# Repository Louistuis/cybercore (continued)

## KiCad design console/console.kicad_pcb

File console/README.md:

# CyberCore Console (rev 0.2, proof of concept)

A slim, black, console-sized box that runs **DeepSeek V3.1 (671B)** locally, on our own carrier board with
**4 × NVIDIA Jetson T5000 (AGX Thor) modules**. Each module has 128 GB of memory, so there is **512 GB in total**.

## What's on the board
| Block | What | Status |
|---|---|---|
| Compute | 4 × Jetson T5000 module (87 × 100 mm), 699-pin Molex Mirror Mezz 203456-0003, 2.5 mm connector = **5 mm** between board and module | Pin map **real** (NVIDIA). Contact grid **real** (Molex drawing 2034560003). Outline, connector position and standoffs **measured** from NVIDIA's drawings |
| Memory | 4 × 128 GB LPDDR5X = 512 GB (273 GB/s per module, per NVIDIA's spec) | On the modules |
| Module-to-module | Full mesh: each module's MGBE C0-C2 (UPHY lanes 12-14) wired straight to the 3 others, 6 links, AC caps on the back | Nets real, routed by the autorouter (not yet length-matched) |
| Network clock | One 156.25 MHz HCSL oscillator per module (SCTF SX5DF156.250B20F30HNN) into UPHY_REFCLK2, terminated as in DG-12084 fig. 7-12 (33.2 Ω series, 49.9 Ω to GND) | **Real**: pinout and land pattern from SCTF's 5Z spec sheet, which asks for the same 33 Ω / 50 Ω load |
| Uplink | Each module's MGBE C3 → one lane of a QSFP28 cage (4 × 25G breakout = one port per module). TE 2170704 press-fit cage + 38-pin connector, cage end at the rear edge | **Real**: cage layout from TE's drawing 2170704 rev G8, contact pads from SFF-8662 table 6-3 |
| Storage | 1 × M.2 2280 NVMe per module on the back (PCIe C5 x4, UPHY lanes 8-11), each holding its share of the model | Nets real, stock footprint |
| Power | 12 V in through 2 × EPS-style Mini-Fit Jr 8-pin (~600 W). See the power section | Real TI parts and land patterns |
| Management | Per module: 2×20 1.27 mm header (sequencing, reset, recovery, thermal, debug UART, I2C, eFuse enables). One system header: buck enable, PMBus, power-good, current monitors, QSFP sideband | Real connectors. The management board that plugs in is in `../mgmt/` |
| Service | 4 × USB-C on the rear (each module's USB0, used for recovery and flashing) | Real |
| Front | The black **CyberCore status panel** (`../panel/`) plugs into J3 (module 0's USB1 + 5 V) | Panel is finished and orderable |
| Cooling | 4 fan headers, each module driving its own blower (FAN_PWM / FAN_TACH) | Real connectors; the thermal design is not done |

Board: 240 × 256 mm, 12 layers (HDI rules: 0.10 mm clearance), 1.6 mm, **black solder mask, ENIG**.
With the 2.5 mm connector, NVIDIA allows **no parts under a module** on the top side. The module footprint carries a keep-out rule area, so DRC fails if anything lands there.
Everything that belongs to a module (eFuses, load switch, clock, AC caps, M.2 drive, management header) sits on the **back**, right under it.

## Power
| Rail | Part | Setting |
|---|---|---|
| 12 V → 5 V, 20 A | TI **TPS546B24A** (LQFN-CLIP-40, LCSC C3189423) + Coilcraft XAL7070 1 µH, 6 × 47 µF out | Pin straps: 5.0 V, 550 kHz, 3 ms soft start, compensation config 23 (TI's procedure), PMBus 0x10. Enabled by management |
| 12 V → 3.3 V, 20 A | TI **TPS546B24A**, same power stage | Pin straps: 3.32 V, PMBus 0x11. Always on (standby rail), starts at ~8.4 V in |
| Module SYS_VIN_HV (12 V) | TI **TPS25982** eFuse per module (VQFN-24, LCSC C2155761) | 13.4 A limit (T5000 ≈ 130 W ≈ 11 A), latch-off on fault, current monitor to the system header |
| Module SYS_VIN_MV (5 V) | TI **TPS25982** per module | 6.5 A limit, just above NVIDIA's 6 A absolute maximum (DS-11945 table 6-2) |
| Module SYS_VIN_SV (3.3 V) | TI **TPS22918** load switch per module (SOT-23-6, LCSC C131941) | Quick output discharge on, so SV falls after HV and MV |

Each converter's footprint was drawn from TI's own land-pattern drawing (RVF0040A, RGE0024M). The strap resistor values come from the TPS546B24A datasheet tables.

## The model math (DeepSeek V3.1)
- **Size:** 671B parameters at 4-bit ≈ 380-400 GB.
  - 512 GB minus each module's OS share leaves ~460 GB, so it fits with ~50 GB for context cache.
  - 8-bit (~700 GB) does **not** fit.
- **Per token:** 37B active parameters ≈ 18.5 GB read per token.
- **Speed:**
  - Layers split across the 4 modules (pipeline): one module works at a time, so the ceiling is 273 GB/s ÷ 18.5 GB ≈ **15 tok/s**.
  - Experts split across all 4 modules working at once over the 25G mesh: the ceiling is ~1.1 TB/s ÷ 18.5 GB ≈ **59 tok/s**. Mesh latency on every layer eats into that.
  - **Estimate: about 10-25 tok/s for one user.** Measure it before believing it.
  - For scale: a 512 GB Apple Mac Studio does ~17-25 tok/s on this model, and hosted datacenter services ~200.
- **Power:** ~520 W for the modules at full power + NVMe + fans ≈ 600 W.
- **Module cost:** NVIDIA lists the T5000 at $4,999 each (1,000-unit price), so ~$20k for 4 before the board and case.

## Build status (honest)
**Real now:**
- Board outline and the 12-layer black stackup
- Every connection the board makes to each module's 699 pins, taken from NVIDIA's pin description spreadsheet: power, GND, PCIe, MGBE, MGBE clock, USB, management
- Module outline, connector position and the 4 standoff holes, measured from NVIDIA's drawings
- Power: TI bucks, eFuses and load switches with their real land patterns and set-up resistors
- MGBE clock: SCTF oscillator with the maker's pinout and land pattern (pin 1 = enable, high or open runs it)
- QSFP28: TE 2170704 cage layout (sheet 15) with SFF-8662 contact pads: 2 alignment holes, 12 press-fit cage holes, 38 contacts and the cage keep-out, which DRC enforces
- Mirror Mezz contact grid from Molex's drawing
- Stock connectors (M.2, USB-C, Mini-Fit Jr, fan headers, management headers)
- DRC of the placed board (`console.kicad_pcb`): 0 violations
- **Routed** (`console_routed.kicad_pcb`): every connection made, 0 unconnected. See the routing section below

**Confirmed from the makers' own documents:**
- Mirror Mezz contact grid: Molex drawing 2034560003 sheet 2. 699 round 0.50 mm pads (0.60 mm mask opening), rows 1.50 mm apart, 0.90 mm pitch with a 1.30 mm gap between pair groups, alternate rows shifted 0.20 mm. This replaced the uniform 0.96 mm grid measured from NVIDIA's pictures, which was off by up to 0.4 mm.
- QSFP28 contact pads: 0.35 × 1.80 mm, SFF-8662 rev 2.9 table 6-3, which also matches every position measured from TE's drawing.
- 5 V module current: NVIDIA DS-11945 v1.4 table 6-2 gives 6 A absolute maximum, so the eFuse limit is now 6.5 A (226 Ω).

**Still to check:**
1. **Buck compensation (bench).** Config 23 (current-loop gain 6, voltage-loop gain 2) follows TI's procedure in the TPS546B24A datasheet (section 8.2.2.10). It is a stable starting point; measure gain and phase margin on the first board, then raise the gains over PMBus.
2. **MV_LSW_MON (pin L42).** NVIDIA's pin spreadsheet names it but no document describes it, so it is left unconnected. Ask NVIDIA before ordering.
3. **Module position (±0.5 mm).** The connector's place on the module and the standoff holes are still measured from NVIDIA's drawings. NVIDIA's reference carrier design files would pin these down exactly.

**Open questions:**
- **The direct MGBE-to-MGBE mesh.** XFI is meant to drive an SFP+ module. A short PCB link acts like a passive copper cable, but it must be checked against design guide section 7.3.
- **25 GbE speed.** NVIDIA says it is "being validated", so plan on 10G per link until it is confirmed.
- **Sequencing.** Every module has its own SYS_VIN_SV → MV/HV → MODULE_POWER_ON sequence (DG-12084 chapter 5). The eFuses and switches are on this board; the logic that drives them is on the management board (`../mgmt/SEQUENCING.md`).
- **Cooling.** ~540 W in a slim box. The enclosure concept and its hand-calculated cooling budget are in `../enclosure/`; there is no thermal simulation yet.

**Not done:** signal-integrity routing of the high-speed pairs (see below), and power and thermal simulation.

## Routing

The signal layers (F.Cu, In2, In4, In10, B.Cu) of `console_routed.kicad_pcb`. The other 7 layers are ground and power planes, with one 5 V and one 20 V island per module.

- **All 502 connections routed** by Freerouting in 5 passes (7 h 50 min on one CPU core). KiCad's DRC finds **0 unconnected items, 0 clearance errors**.
- **70 track segments are thinner than the 0.09 mm board minimum** (53 mm in all, most under 0.5 mm long). They're where the autorouter narrowed a track to leave a fine-pitch pad, mostly at the Mirror Mezz connectors. 65 are 0.075 mm, which HDI fabs make, and 5 are 0.05-0.06 mm, which need a hand fix. `route_finish.py` already widened every segment that had room.
- **Not signal-integrity routed.** The autorouter routes each wire of a differential pair on its own. The 25G mesh, PCIe Gen4, USB and QSFP pairs still need routing as coupled, impedance-controlled and length-matched pairs. Treat this file as proof that the board can be fully connected on 12 layers, not as an orderable layout.

## Rebuild
1. Download NVIDIA's *Jetson Thor Series Modules Design Guide* (DG-12084-001, free from developer.nvidia.com).
2. Extract its attachments: `pdfdetach -saveall -o datasheets/nv_attach <guide.pdf>`.
3. Run the build script with KiCad's Python:
```
/Applications/KiCad/KiCad.app/Contents/Frameworks/Python.framework/Versions/Current/bin/python3 make_console.py
kicad-cli pcb drc -o drc.rpt console.kicad_pcb
```
4. Route it (about 8 hours on one core; commands in `route.py`): `route.py prep`, then Freerouting, then `route.py import` and `route_finish.py`.
NVIDIA's documents and the pin spreadsheet are **not** in this repo; the script reads them from your own download. The TI datasheets used for the power stage are free on ti.com (TPS546B24A, TPS25982, TPS22918). The QSFP28 layout comes from TE's customer drawing 2170704 (te.com) and SFF-8662 (snia.org); the connector grid from Molex drawing 2034560003 (molex.com).

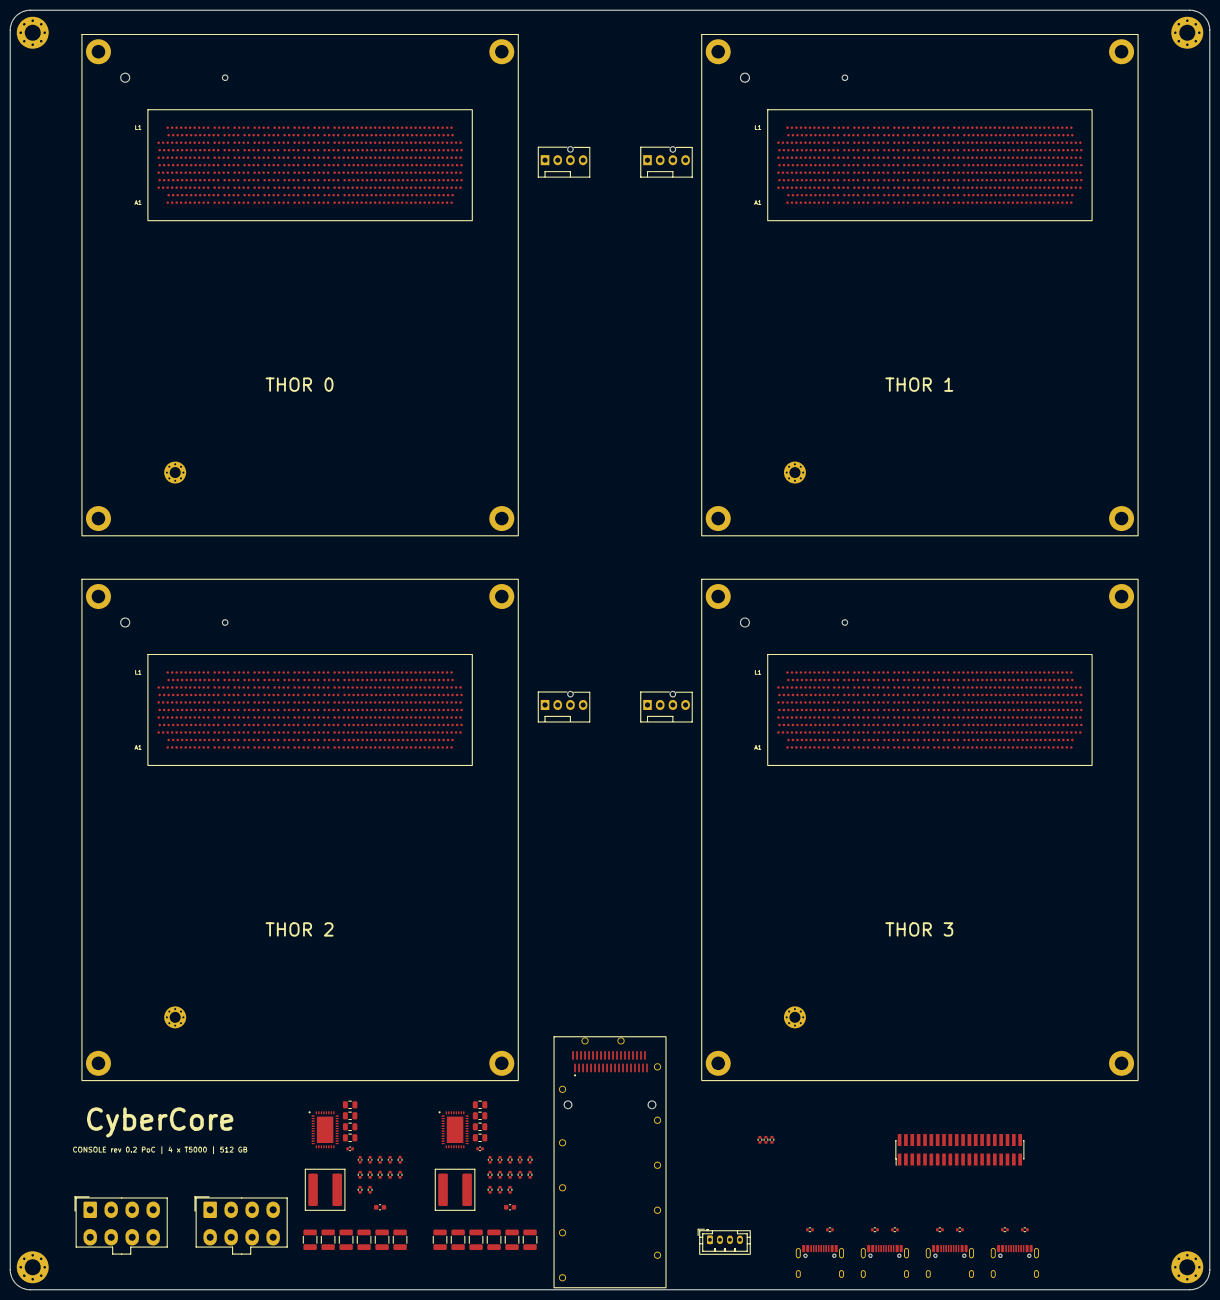
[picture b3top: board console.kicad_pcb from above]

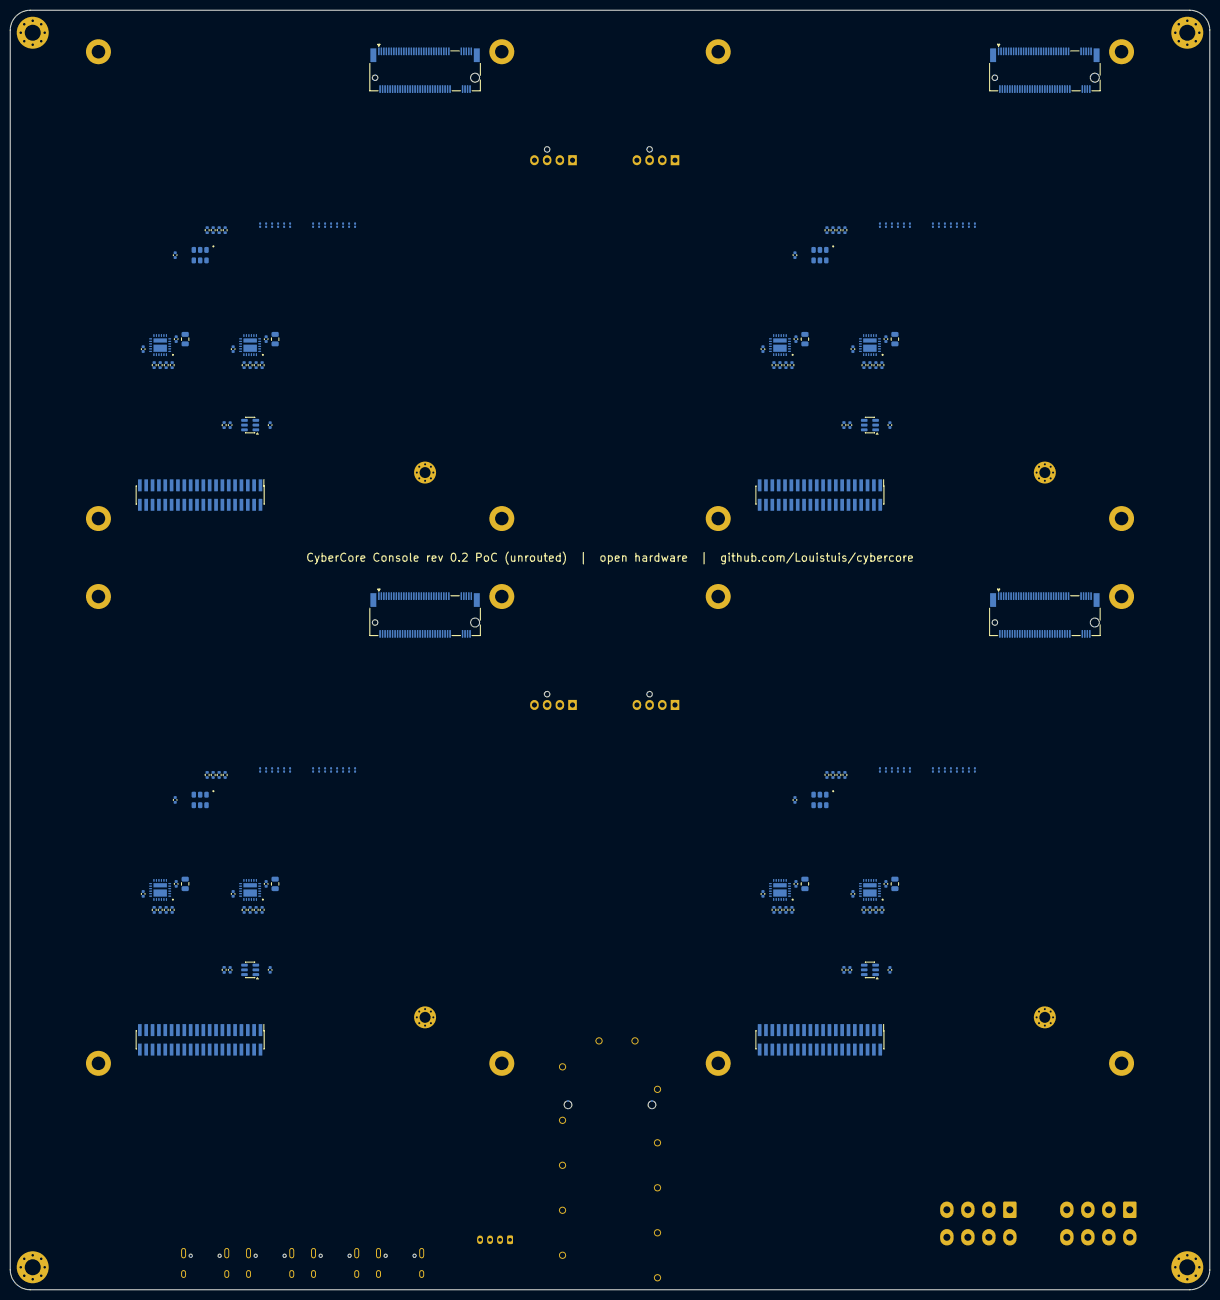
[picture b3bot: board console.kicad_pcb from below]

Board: 12 copper layers, 240.0 x 256.0 mm, 257 parts (172 on the bottom side), 384 nets, no tracks yet.

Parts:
C101, C111, C201, C211, C301, C311, C401, C411, C501, C502, C503, C504, C601, C602, C603, C604: 22uF; C_0805_2012Metric
C102, C112, C140, C202, C212, C240, C302, C312, C340, C402, C412, C440, C522, C622: 100nF; C_0402_1005Metric
C103, C203, C303, C403, C505, C605: 10nF; C_0402_1005Metric
C113, C213, C313, C413: 3.3nF; C_0402_1005Metric
C121, C221, C321, C421, C521, C523, C621, C623: 1uF; C_0402_1005Metric
C122, C222, C322, C422: 1nF; C_0402_1005Metric
C150, C151, C152, C153, C154, C155, C156, C157, C158, C159, C160, C161, C162, C163, C250, C251, C252, C253, C254, C255, C256, C257, C258, C259, C260, C261, C262, C263, C350, C351, C352, C353, C354, C355, C356, C357, C358, C359, C360, C361, C362, C363, C450, C451, C452, C453, C454, C455, C456, C457, C458, C459, C460, C461, C462, C463: 100nF; C_0201_0603Metric
C511, C512, C513, C514, C515, C516, C611, C612, C613, C614, C615, C616: 47uF; C_1210_3225Metric
C531, C631: 4.7uF; C_0603_1608Metric
H1, H2, H3, H4: case; MountingHole_3.2mm_M3_Pad_Via
H10, H11, H12, H13: M.2 standoff; MountingHole_2.2mm_M2_Pad_Via
J1, J5: 12V IN (EPS 8-pin); Molex_Mini-Fit_Jr_5566-08A_2x04_P4.20mm_Vertical
J2: QSFP28 4x25G uplink; TE_2170704_QSFP28_Cage_SFF8679_38P
J3: STATUS PANEL; JST_PH_B4B-PH-K_1x04_P2.00mm_Vertical
J4: SYS MGMT; PinHeader_2x20_P1.27mm_Vertical_SMD
J10, J11, J12, J13: M.2 2280 NVMe 4 TB; TE_M.2_M_2x38-1MP_P0.5mm
J20: MGMT M0; PinHeader_2x20_P1.27mm_Vertical_SMD
J21: MGMT M1; PinHeader_2x20_P1.27mm_Vertical_SMD
J22: MGMT M2; PinHeader_2x20_P1.27mm_Vertical_SMD
J23: MGMT M3; PinHeader_2x20_P1.27mm_Vertical_SMD
J30: FAN M0; FanPinHeader_1x04_P2.54mm_Vertical
J31: FAN M1; FanPinHeader_1x04_P2.54mm_Vertical
J32: FAN M2; FanPinHeader_1x04_P2.54mm_Vertical
J33: FAN M3; FanPinHeader_1x04_P2.54mm_Vertical
J40: USB-C M0 recovery; USB_C_Receptacle_HRO_TYPE-C-31-M-12
J41: USB-C M1 recovery; USB_C_Receptacle_HRO_TYPE-C-31-M-12
J42: USB-C M2 recovery; USB_C_Receptacle_HRO_TYPE-C-31-M-12
J43: USB-C M3 recovery; USB_C_Receptacle_HRO_TYPE-C-31-M-12
L501, L601: XAL7070-102MEC 1uH (C6609502); L_Coilcraft_XAL7070-XXX
R10, R11, R12, R13, R14, R15, R16, R17: 5.1k; R_0402_1005Metric
R101, R201, R301, R401: 110; R_0402_1005Metric
R102, R202, R302, R402: 470; R_0402_1005Metric
R103, R113, R121, R203, R213, R221, R303, R313, R321, R403, R413, R421, R503, R603: 100k; R_0402_1005Metric
R104, R114, R204, R214, R304, R314, R404, R414, R502, R602, R703: 10k; R_0402_1005Metric
R111, R211, R311, R411: 226; R_0402_1005Metric
R112, R212, R312, R412: 1k; R_0402_1005Metric
R140, R141, R240, R241, R340, R341, R440, R441: 33.2; R_0402_1005Metric
R142, R143, R242, R243, R342, R343, R442, R443: 49.9; R_0402_1005Metric
R501, R601: 10; R_0402_1005Metric
R504: 1.87k; R_0402_1005Metric
R505, R605: 12.1k; R_0402_1005Metric
R506, R607: 56.2k; R_0402_1005Metric
R507, R608: 11.5k; R_0402_1005Metric
R508, R509, R609: 4.64k; R_0402_1005Metric
R604: 15k; R_0402_1005Metric
R606: 21.5k; R_0402_1005Metric
R610: 5.62k; R_0402_1005Metric
R701, R702: 4.7k; R_0402_1005Metric
U1, U2, U3, U4: Jetson T5000 (AGX Thor) 128 GB; Jetson_T5000_Module_MirrorMezz699_Carrier
U101, U102, U201, U202, U301, U302, U401, U402: TPS259827ONRGER (C2155761); TI_RGE0024M_VQFN-24_4x4mm_P0.5mm_SplitPad
U103, U203, U303, U403: TPS22918DBVR (C131941); SOT-23-6
U501, U601: TPS546B24ARVFR (C3189423); TI_RVF0040A_LQFN-CLIP-40_5x7mm_P0.5mm_EP3.3x5.3mm
X1, X2, X3, X4: 156.25MHz HCSL; SCTF_5Z_SMD5032-6P_5.0x3.2mm

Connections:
3V3: C121.1, C140.1, C221.1, C240.1, C321.1, C340.1, C421.1, C440.1, C611.1, C612.1, C613.1, C614.1, C615.1, C616.1, J2.10, J2.29, J2.30, J4.39, J10.2, J10.4, J10.12, J10.14, J10.16, J10.18, J10.70, J10.72, J10.74, J11.2, J11.4, J11.12, J11.14, J11.16, J11.18, J11.70, J11.72, J11.74, J12.2, J12.4, J12.12, J12.14, J12.16, J12.18, J12.70, J12.72, J12.74, J13.2, J13.4, J13.12, J13.14, J13.16, J13.18, J13.70, J13.72, J13.74, J20.39, J21.39, J22.39, J23.39, L601.2, R104.1, R114.1, R204.1, R214.1, R304.1, R314.1, R404.1, R414.1, R502.1, R602.1, R701.1, R702.1, R703.1, U103.1, U203.1, U303.1, U403.1, U601.33, X1.1, X1.6, X2.1, X2.6, X3.1, X3.6, X4.1, X4.6
5V: C111.1, C112.1, C211.1, C212.1, C311.1, C312.1, C411.1, C412.1, C511.1, C512.1, C513.1, C514.1, C515.1, C516.1, J3.1, L501.2, U102.1, U102.2, U102.3, U102.16, U102.25, U202.1, U202.2, U202.3, U202.16, U202.25, U302.1, U302.2, U302.3, U302.16, U302.25, U402.1, U402.2, U402.3, U402.16, U402.25, U501.33
BUCK3_EN: R603.2, R604.1, U601.27
BUCK3_PG: R602.2, U601.1
BUCK5_EN: J4.1, R503.1, U501.27
BUCK5_PG: J4.3, R502.2, U501.1
GND: C101.2, C102.2, C103.2, C111.2, C112.2, C113.2, C121.2, C122.2, C140.2, C201.2, C202.2, C203.2, C211.2, C212.2, C213.2, C221.2, C222.2, C240.2, C301.2, C302.2, C303.2, C311.2, C312.2, C313.2, C321.2, C322.2, C340.2, C401.2, C402.2, C403.2, C411.2, C412.2, C413.2, C421.2, C422.2, C440.2, C501.2, C502.2, C503.2, C504.2, C505.2, C511.2, C512.2, C513.2, C514.2, C515.2, C516.2, C523.2, C531.2, C601.2, C602.2, C603.2, C604.2, C605.2, C611.2, C612.2, C613.2, C614.2, C615.2, C616.2, C623.2, C631.2, H1.1, H2.1, H3.1, H4.1, H10.1, H11.1, H12.1, H13.1, J1.1, J1.2, J1.3, J1.4, J2.1, J2.4, J2.7, J2.13, J2.16, J2.19, J2.20, J2.23, J2.26, J2.32, J2.35, J2.38, J2.SH, J3.4, J4.2, J4.4, J4.6, J4.8, J4.10, J4.12, J4.14, J4.16, J4.18, J4.20, J4.22, J4.24, J4.26, J4.28, J4.30, J4.32, J4.34, J4.36, J4.38, J4.40, J5.1, J5.2, J5.3, J5.4, J10.3, J10.9, J10.15, J10.21, J10.27, J10.33, J10.39, J10.45, J10.51, J10.57, J10.71, J10.73, J10.75, J10.MP, J11.3, J11.9, J11.15, J11.21, J11.27, J11.33, J11.39, J11.45, J11.51, J11.57, J11.71, J11.73, J11.75, J11.MP, J12.3, J12.9, J12.15, J12.21, J12.27, J12.33, J12.39, J12.45, J12.51, J12.57, J12.71, J12.73, J12.75, J12.MP, J13.3, J13.9, J13.15, J13.21, J13.27, J13.33, J13.39, J13.45, J13.51, J13.57, J13.71, J13.73, J13.75, J13.MP, J20.2, J20.4, J20.6, J20.8, J20.10, J20.12, J20.14, J20.16, J20.18, J20.20, J20.22, J20.24, J20.26, J20.28, J20.30, J20.32, J20.34, J20.36, J20.38, J20.40, J21.2, J21.4, J21.6, J21.8, J21.10, J21.12, J21.14, J21.16, J21.18, J21.20, J21.22, J21.24, J21.26, J21.28, J21.30, J21.32, J21.34, J21.36, J21.38, J21.40, J22.2, J22.4, J22.6, J22.8, J22.10, J22.12, J22.14, J22.16, J22.18, J22.20, J22.22, J22.24, J22.26, J22.28, J22.30, J22.32, J22.34, J22.36, J22.38, J22.40, J23.2, J23.4, J23.6, J23.8, J23.10, J23.12, J23.14, J23.16, J23.18, J23.20, J23.22, J23.24, J23.26, J23.28, J23.30, J23.32, J23.34, J23.36, J23.38, J23.40, J30.1, J31.1, J32.1, J33.1, J40.A1, J40.A12, J40.B1, J40.B12, J40.SH, J41.A1, J41.A12, J41.B1, J41.B12, J41.SH, J42.A1, J42.A12, J42.B1, J42.B12, J42.SH, J43.A1, J43.A12, J43.B1, J43.B12, J43.SH, R10.2, R11.2, R12.2, R13.2, R14.2, R15.2, R16.2, R17.2, R101.2, R102.2, R103.2, R111.2, R112.2, R113.2, R121.2, R142.2, R143.2, R201.2, R202.2, R203.2, R211.2, R212.2, R213.2, R221.2, R242.2, R243.2, R301.2, R302.2, R303.2, R311.2, R312.2, R313.2, R321.2, R342.2, R343.2, R401.2, R402.2, R403.2, R411.2, R412.2, R413.2, R421.2, R442.2, R443.2, R503.2, R505.2, R506.2, R508.2, R509.2, R604.2, R606.2, R607.2, R609.2, R610.2, U1.A9, U1.A12, U1.A13, U1.A16, U1.A17, U1.A20, U1.A21, U1.A24, U1.A25, U1.A28, U1.A29, U1.A32, U1.A33, U1.A36, U1.A37, U1.A40, U1.A43, U1.A46, U1.A49, U1.A52, U1.A63, U1.B4, U1.B7, U1.B11, U1.B14, U1.B15, U1.B18, U1.B19, U1.B22, U1.B23, U1.B26, U1.B27, U1.B30, U1.B31, U1.B34, U1.B35, U1.B38, U1.B39, U1.B41, U1.B44, U1.B47, U1.B50, U1.B53, U1.B57, U1.C3, U1.C9, U1.C12, U1.C13, U1.C16, U1.C17, U1.C20, U1.C21, U1.C24, U1.C25, U1.C28, U1.C29, U1.C32, U1.C33, U1.C36, U1.C37, U1.C40, U1.C43, U1.C46, U1.C49, U1.C52, U1.C62, U1.D4, U1.D7, U1.D11, U1.D14, U1.D15, U1.D18, U1.D19, U1.D22, U1.D23, U1.D26, U1.D27, U1.D30, U1.D31, U1.D34, U1.D35, U1.D38, U1.D39, U1.D41, U1.D44, U1.D47, U1.D50, U1.D53, U1.D57, U1.D63, U1.E3, U1.E9, U1.E12, U1.E13, U1.E16, U1.E17, U1.E20, U1.E21, U1.E24, U1.E25, U1.E28, U1.E29, U1.E32, U1.E33, U1.E36, U1.E37, U1.E40, U1.E43, U1.E46, U1.E49, U1.E52, U1.E57, U1.E62, U1.F4, U1.F7, U1.F11, U1.F14, U1.F15, U1.F18, U1.F19, U1.F22, U1.F23, U1.F26, U1.F27, U1.F30, U1.F31, U1.F34, U1.F35, U1.F38, U1.F39, U1.F41, U1.F44, U1.F47, U1.F50, U1.F57, U1.F62, U1.G3, U1.G9, U1.G12, U1.G13, U1.G16, U1.G17, U1.G20, U1.G21, U1.G24, U1.G25, U1.G28, U1.G29, U1.G32, U1.G33, U1.G36, U1.G37, U1.G40, U1.G43, U1.G46, U1.G49, U1.G52, U1.G57, U1.G62, U1.H4, U1.H7, U1.H11, U1.H14, U1.H15, U1.H18, U1.H19, U1.H22, U1.H23, U1.H26, U1.H27, U1.H30, U1.H31, U1.H34, U1.H35, U1.H38, U1.H39, U1.H41, U1.H44, U1.H47, U1.H50, U1.H56, U1.H63, U1.J3, U1.J8, U1.J12, U1.J13, U1.J16, U1.J17, U1.J20, U1.J21, U1.J24, U1.J25, U1.J28, U1.J29, U1.J32, U1.J33, U1.J36, U1.J37, U1.J40, U1.J43, U1.J46, U1.J49, U1.J56, U1.J62, U1.K4, U1.K8, U1.K11, U1.K14, U1.K15, U1.K18, U1.K19, U1.K22, U1.K23, U1.K26, U1.K27, U1.K30, U1.K31, U1.K34, U1.K35, U1.K38, U1.K39, U1.K41, U1.K42, U1.K45, U1.K48, U1.K55, U1.K63, U1.L3, U1.L7, U1.L12, U1.L13, U1.L16, U1.L17, U1.L20, U1.L21, U1.L24, U1.L25, U1.L28, U1.L29, U1.L32, U1.L33, U1.L36, U1.L37, U1.L40, U1.L43, U1.L46, U1.MH, U2.A9, U2.A12, U2.A13, U2.A16, U2.A17, U2.A20, U2.A21, U2.A24, U2.A25, U2.A28, U2.A29, U2.A32, U2.A33, U2.A36, U2.A37, U2.A40, U2.A43, U2.A46, U2.A49, U2.A52, U2.A63, U2.B4, U2.B7, U2.B11, U2.B14, U2.B15, U2.B18, U2.B19, U2.B22, U2.B23, U2.B26, U2.B27, U2.B30, U2.B31, U2.B34, U2.B35, U2.B38, U2.B39, U2.B41, U2.B44, U2.B47, U2.B50, U2.B53, U2.B57, U2.C3, U2.C9, U2.C12, U2.C13, U2.C16, U2.C17, U2.C20, U2.C21, U2.C24, U2.C25, U2.C28, U2.C29, U2.C32, U2.C33, U2.C36, U2.C37, U2.C40, U2.C43, U2.C46, U2.C49, U2.C52, U2.C62, U2.D4, U2.D7, U2.D11, U2.D14, U2.D15, U2.D18, U2.D19, U2.D22, U2.D23, U2.D26, U2.D27, U2.D30, U2.D31, U2.D34, U2.D35, U2.D38, U2.D39, U2.D41, U2.D44, U2.D47, U2.D50, U2.D53, U2.D57, U2.D63, U2.E3, U2.E9, U2.E12, U2.E13, U2.E16, U2.E17, U2.E20, U2.E21, U2.E24, U2.E25, U2.E28, U2.E29, U2.E32, U2.E33, U2.E36, U2.E37, U2.E40, U2.E43, U2.E46, U2.E49, U2.E52, U2.E57, U2.E62, U2.F4, U2.F7, U2.F11, U2.F14, U2.F15, U2.F18, U2.F19, U2.F22, U2.F23, U2.F26, U2.F27, U2.F30, U2.F31, U2.F34, U2.F35, U2.F38, U2.F39, U2.F41, U2.F44, U2.F47, U2.F50, U2.F57, U2.F62, U2.G3, U2.G9, U2.G12, U2.G13, U2.G16, U2.G17, U2.G20, U2.G21, U2.G24, U2.G25, U2.G28, U2.G29, U2.G32, U2.G33, U2.G36, U2.G37, U2.G40, U2.G43, U2.G46, U2.G49, U2.G52, U2.G57, U2.G62, U2.H4, U2.H7, U2.H11, U2.H14, U2.H15, U2.H18, U2.H19, U2.H22, U2.H23, U2.H26, U2.H27, U2.H30, U2.H31, U2.H34, U2.H35, U2.H38, U2.H39, U2.H41, U2.H44, U2.H47, U2.H50, U2.H56, U2.H63, U2.J3, U2.J8, U2.J12, U2.J13, U2.J16, U2.J17, U2.J20, U2.J21, U2.J24, U2.J25, U2.J28, U2.J29, U2.J32, U2.J33, U2.J36, U2.J37, U2.J40, U2.J43, U2.J46, U2.J49, U2.J56, U2.J62, U2.K4, U2.K8, U2.K11, U2.K14, U2.K15, U2.K18, U2.K19, U2.K22, U2.K23, U2.K26, U2.K27, U2.K30, U2.K31, U2.K34, U2.K35, U2.K38, U2.K39, U2.K41, U2.K42, U2.K45, U2.K48, U2.K55, U2.K63, U2.L3, U2.L7, U2.L12, U2.L13, U2.L16, U2.L17, U2.L20, U2.L21, U2.L24, U2.L25, U2.L28, U2.L29, U2.L32, U2.L33, U2.L36, U2.L37, U2.L40, U2.L43, U2.L46, U2.MH, U3.A9, U3.A12, U3.A13, U3.A16, U3.A17, U3.A20, U3.A21, U3.A24, U3.A25, U3.A28, U3.A29, U3.A32, U3.A33, U3.A36, U3.A37, U3.A40, U3.A43, U3.A46, U3.A49, U3.A52, U3.A63, U3.B4, U3.B7, U3.B11, U3.B14, U3.B15, U3.B18, U3.B19, U3.B22, U3.B23, U3.B26, U3.B27, U3.B30, U3.B31, U3.B34, U3.B35, U3.B38, U3.B39, U3.B41, U3.B44, U3.B47, U3.B50, U3.B53, U3.B57, U3.C3, U3.C9, U3.C12, U3.C13, U3.C16, U3.C17, U3.C20, U3.C21, U3.C24, U3.C25, U3.C28, U3.C29, U3.C32, U3.C33, U3.C36, U3.C37, U3.C40, U3.C43, U3.C46, U3.C49, U3.C52, U3.C62, U3.D4, U3.D7, U3.D11, U3.D14, U3.D15, U3.D18, U3.D19, U3.D22, U3.D23, U3.D26, U3.D27, U3.D30, U3.D31, U3.D34, U3.D35, U3.D38, U3.D39, U3.D41, U3.D44, U3.D47, U3.D50, U3.D53, U3.D57, U3.D63, U3.E3, U3.E9, U3.E12, U3.E13, U3.E16, U3.E17, U3.E20, U3.E21, U3.E24, U3.E25, U3.E28, U3.E29, U3.E32, U3.E33, U3.E36, U3.E37, U3.E40, U3.E43, U3.E46, U3.E49, U3.E52, U3.E57, U3.E62, U3.F4, U3.F7, U3.F11, U3.F14, U3.F15, U3.F18, U3.F19, U3.F22, U3.F23, U3.F26, U3.F27, U3.F30, U3.F31, U3.F34, U3.F35, U3.F38, U3.F39, U3.F41, U3.F44, U3.F47, U3.F50, U3.F57, U3.F62, U3.G3, U3.G9, U3.G12, U3.G13, U3.G16, U3.G17, U3.G20, U3.G21, U3.G24, U3.G25, U3.G28, U3.G29, U3.G32, U3.G33, U3.G36, U3.G37, U3.G40, U3.G43, U3.G46, U3.G49, U3.G52, U3.G57, U3.G62, U3.H4, U3.H7, U3.H11, U3.H14, U3.H15, U3.H18, U3.H19, U3.H22, U3.H23, U3.H26, U3.H27, U3.H30, U3.H31, U3.H34, U3.H35, U3.H38, U3.H39, U3.H41, U3.H44, U3.H47, U3.H50, U3.H56, U3.H63, U3.J3, U3.J8, U3.J12, U3.J13, U3.J16, U3.J17, U3.J20, U3.J21, U3.J24, U3.J25, U3.J28, U3.J29, U3.J32, U3.J33, U3.J36, U3.J37, U3.J40, U3.J43, U3.J46, U3.J49, U3.J56, U3.J62, U3.K4, U3.K8, U3.K11, U3.K14, U3.K15, U3.K18, U3.K19, U3.K22, U3.K23, U3.K26, U3.K27, U3.K30, U3.K31, U3.K34, U3.K35, U3.K38, U3.K39, U3.K41, U3.K42, U3.K45, U3.K48, U3.K55, U3.K63, U3.L3, U3.L7, U3.L12, U3.L13, U3.L16, U3.L17, U3.L20, U3.L21, U3.L24, U3.L25, U3.L28, U3.L29, U3.L32, U3.L33, U3.L36, U3.L37, U3.L40, U3.L43, U3.L46, U3.MH, U4.A9, U4.A12, U4.A13, U4.A16, U4.A17, U4.A20, U4.A21, U4.A24, U4.A25, U4.A28, U4.A29, U4.A32, U4.A33, U4.A36, U4.A37, U4.A40, U4.A43, U4.A46, U4.A49, U4.A52, U4.A63, U4.B4, U4.B7, U4.B11, U4.B14, U4.B15, U4.B18, U4.B19, U4.B22, U4.B23, U4.B26, U4.B27, U4.B30, U4.B31, U4.B34, U4.B35, U4.B38, U4.B39, U4.B41, U4.B44, U4.B47, U4.B50, U4.B53, U4.B57, U4.C3, U4.C9, U4.C12, U4.C13, U4.C16, U4.C17, U4.C20, U4.C21, U4.C24, U4.C25, U4.C28, U4.C29, U4.C32, U4.C33, U4.C36, U4.C37, U4.C40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
M0_CARRIER_POWER_ON: J20.3, U1.L62
M0_CC1: J40.A5, R10.1
M0_CC2: J40.B5, R11.1
M0_FAN_PWM: J30.4, U1.K62
M0_FAN_TACH: J30.3, U1.E54
M0_FORCE_RECOVERY_N: J20.11, U1.L10
M0_HV_EN: J20.31, R103.1, U101.6
M0_HV_IMON: J4.17, R102.1, U101.9
M0_HV_PG: J20.33, R104.2, U101.13
M0_I2C3_CLK: J20.27, U1.F53
M0_I2C3_DAT: J20.29, U1.E53
M0_MGBE_REFCLK_N: R141.2, R143.1, U1.F29
M0_MGBE_REFCLK_P: R140.2, R142.1, U1.F28
M0_MODULE_POWER_GOOD: J20.7, U1.L59
M0_MODULE_POWER_ON: J20.1, U1.L54
M0_MODULE_SHDN_N: J20.13, U1.L52
M0_MV_EN: J20.35, R113.1, U102.6
M0_MV_IMON: R112.1, U102.9
M0_MV_PG: J4.9, R114.2, U102.13
M0_OSC_N: R141.1, X1.5
M0_OSC_P: R140.1, X1.4
M0_PCIE_CLKREQ_N: J10.52, U1.L19
M0_PCIE_PERST_N: J10.50, U1.L18
M0_PCIE_REFCLK_N: J10.53, U1.F33
M0_PCIE_REFCLK_P: J10.55, U1.F32
M0_PCIE_RX0_N: J10.47, U1.D25
M0_PCIE_RX0_P: J10.49, U1.D24
M0_PCIE_RX1_N: J10.35, U1.B24
M0_PCIE_RX1_P: J10.37, U1.B25
M0_PCIE_RX2_N: J10.23, U1.C26
M0_PCIE_RX2_P: J10.25, U1.C27
M0_PCIE_RX3_N: J10.11, U1.A27
M0_PCIE_RX3_P: J10.13, U1.A26
M0_PCIE_TX0_N: C151.2, J10.41
M0_PCIE_TX0_N_AC: C151.1, U1.H25
M0_PCIE_TX0_P: C150.2, J10.43
M0_PCIE_TX0_P_AC: C150.1, U1.H24
M0_PCIE_TX1_N: C153.2, J10.29
M0_PCIE_TX1_N_AC: C153.1, U1.K24
M0_PCIE_TX1_P: C152.2, J10.31
M0_PCIE_TX1_P_AC: C152.1, U1.K25
M0_PCIE_TX2_N: C155.2, J10.17
M0_PCIE_TX2_N_AC: C155.1, U1.G26
M0_PCIE_TX2_P: C154.2, J10.19
M0_PCIE_TX2_P_AC: C154.1, U1.G27
M0_PCIE_TX3_N: C157.2, J10.5
M0_PCIE_TX3_N_AC: C157.1, U1.J27
M0_PCIE_TX3_P: C156.2, J10.7
M0_PCIE_TX3_P_AC: C156.1, U1.J26
M0_PCIE_WAKE_N: J10.54, U1.A8
M0_PRSNT0: J20.19, U1.A3
M0_PRSNT1: J20.21, U1.L63
M0_SV_EN: J20.37, R121.1, U103.3
M0_SYS_RESET_N: J20.5, U1.L60
M0_THERM_ALERT_N: J20.15, U1.L56
M0_THERM_SHDN_REQ_N: J20.17, U1.G59
M0_UART3_RX_DEBUG: J20.25, U1.K60
M0_UART3_TX_DEBUG: J20.23, U1.H62
M0_USB0_N: J40.A7, J40.B7, U1.F13
M0_USB0_P: J40.A6, J40.B6, U1.F12
M0_USB_VBUS: J40.A4, J40.A9, J40.B4, J40.B9
M0_VDDIN_PWR_BAD_N: J20.9, U1.L55
M0_VIN_HV: U1.B3, U1.B63, U1.C1, U1.C2, U1.C63, U1.C64, U1.C65, U1.D1, U1.D2, U1.D3, U1.D64, U1.D65, U1.E1, U1.E2, U1.E63, U1.E64, U1.E65, U1.F1, U1.F2, U1.F3, U1.F63, U1.F64, U1.F65, U1.G1, U1.G2, U1.G63, U1.G64, U1.G65, U1.H1, U1.H2, U1.H3, U1.H64, U1.H65, U1.J1, U1.J2, U1.J63, U1.J64, U1.J65, U1.K3, U101.17, U101.18, U101.19, U101.20, U101.21, U101.22, U101.23, U101.24
M0_VIN_MV: U1.L22, U1.L23, U1.L26, U1.L27, U1.L30, U1.L31, U1.L34, U1.L35, U1.L38, U1.L39, U102.17, U102.18, U102.19, U102.20, U102.21, U102.22, U102.23, U102.24
M0_VIN_SV: U1.L53, U103.5, U103.6
M1_CARRIER_POWER_ON: J21.3, U2.L62
M1_CC1: J41.A5, R12.1
M1_CC2: J41.B5, R13.1
M1_FAN_PWM: J31.4, U2.K62
M1_FAN_TACH: J31.3, U2.E54
M1_FORCE_RECOVERY_N: J21.11, U2.L10
M1_HV_EN: J21.31, R203.1, U201.6
M1_HV_IMON: J4.19, R202.1, U201.9
M1_HV_PG: J21.33, R204.2, U201.13
M1_I2C3_CLK: J21.27, U2.F53
M1_I2C3_DAT: J21.29, U2.E53
M1_MGBE_REFCLK_N: R241.2, R243.1, U2.F29
M1_MGBE_REFCLK_P: R240.2, R242.1, U2.F28
M1_MODULE_POWER_GOOD: J21.7, U2.L59
M1_MODULE_POWER_ON: J21.1, U2.L54
M1_MODULE_SHDN_N: J21.13, U2.L52
M1_MV_EN: J21.35, R213.1, U202.6
M1_MV_IMON: R212.1, U202.9
M1_MV_PG: J4.11, R214.2, U202.13
M1_OSC_N: R241.1, X2.5
M1_OSC_P: R240.1, X2.4
M1_PCIE_CLKREQ_N: J11.52, U2.L19
M1_PCIE_PERST_N: J11.50, U2.L18
M1_PCIE_REFCLK_N: J11.53, U2.F33
M1_PCIE_REFCLK_P: J11.55, U2.F32
M1_PCIE_RX0_N: J11.47, U2.D25
M1_PCIE_RX0_P: J11.49, U2.D24
M1_PCIE_RX1_N: J11.35, U2.B24
M1_PCIE_RX1_P: J11.37, U2.B25
M1_PCIE_RX2_N: J11.23, U2.C26
M1_PCIE_RX2_P: J11.25, U2.C27
M1_PCIE_RX3_N: J11.11, U2.A27
M1_PCIE_RX3_P: J11.13, U2.A26
M1_PCIE_TX0_N: C251.2, J11.41
M1_PCIE_TX0_N_AC: C251.1, U2.H25
M1_PCIE_TX0_P: C250.2, J11.43
M1_PCIE_TX0_P_AC: C250.1, U2.H24
M1_PCIE_TX1_N: C253.2, J11.29
M1_PCIE_TX1_N_AC: C253.1, U2.K24
M1_PCIE_TX1_P: C252.2, J11.31
M1_PCIE_TX1_P_AC: C252.1, U2.K25
M1_PCIE_TX2_N: C255.2, J11.17
M1_PCIE_TX2_N_AC: C255.1, U2.G26
M1_PCIE_TX2_P: C254.2, J11.19
M1_PCIE_TX2_P_AC: C254.1, U2.G27
M1_PCIE_TX3_N: C257.2, J11.5
M1_PCIE_TX3_N_AC: C257.1, U2.J27
M1_PCIE_TX3_P: C256.2, J11.7
M1_PCIE_TX3_P_AC: C256.1, U2.J26
M1_PCIE_WAKE_N: J11.54, U2.A8
M1_PRSNT0: J21.19, U2.A3
M1_PRSNT1: J21.21, U2.L63
M1_SV_EN: J21.37, R221.1, U203.3
M1_SYS_RESET_N: J21.5, U2.L60
M1_THERM_ALERT_N: J21.15, U2.L56
M1_THERM_SHDN_REQ_N: J21.17, U2.G59
M1_UART3_RX_DEBUG: J21.25, U2.K60
M1_UART3_TX_DEBUG: J21.23, U2.H62
M1_USB0_N: J41.A7, J41.B7, U2.F13
M1_USB0_P: J41.A6, J41.B6, U2.F12
M1_USB_VBUS: J41.A4, J41.A9, J41.B4, J41.B9
M1_VDDIN_PWR_BAD_N: J21.9, U2.L55
M1_VIN_HV: U2.B3, U2.B63, U2.C1, U2.C2, U2.C63, U2.C64, U2.C65, U2.D1, U2.D2, U2.D3, U2.D64, U2.D65, U2.E1, U2.E2, U2.E63, U2.E64, U2.E65, U2.F1, U2.F2, U2.F3, U2.F63, U2.F64, U2.F65, U2.G1, U2.G2, U2.G63, U2.G64, U2.G65, U2.H1, U2.H2, U2.H3, U2.H64, U2.H65, U2.J1, U2.J2, U2.J63, U2.J64, U2.J65, U2.K3, U201.17, U201.18, U201.19, U201.20, U201.21, U201.22, U201.23, U201.24
M1_VIN_MV: U2.L22, U2.L23, U2.L26, U2.L27, U2.L30, U2.L31, U2.L34, U2.L35, U2.L38, U2.L39, U202.17, U202.18, U202.19, U202.20, U202.21, U202.22, U202.23, U202.24
M1_VIN_SV: U2.L53, U203.5, U203.6
M2_CARRIER_POWER_ON: J22.3, U3.L62
M2_CC1: J42.A5, R14.1
M2_CC2: J42.B5, R15.1
M2_FAN_PWM: J32.4, U3.K62
M2_FAN_TACH: J32.3, U3.E54
M2_FORCE_RECOVERY_N: J22.11, U3.L10
M2_HV_EN: J22.31, R303.1, U301.6
M2_HV_IMON: J4.21, R302.1, U301.9
M2_HV_PG: J22.33, R304.2, U301.13
M2_I2C3_CLK: J22.27, U3.F53
M2_I2C3_DAT: J22.29, U3.E53
M2_MGBE_REFCLK_N: R341.2, R343.1, U3.F29
M2_MGBE_REFCLK_P: R340.2, R342.1, U3.F28
M2_MODULE_POWER_GOOD: J22.7, U3.L59
M2_MODULE_POWER_ON: J22.1, U3.L54
M2_MODULE_SHDN_N: J22.13, U3.L52
M2_MV_EN: J22.35, R313.1, U302.6
M2_MV_IMON: R312.1, U302.9
M2_MV_PG: J4.13, R314.2, U302.13
M2_OSC_N: R341.1, X3.5
M2_OSC_P: R340.1, X3.4
M2_PCIE_CLKREQ_N: J12.52, U3.L19
M2_PCIE_PERST_N: J12.50, U3.L18
M2_PCIE_REFCLK_N: J12.53, U3.F33
M2_PCIE_REFCLK_P: J12.55, U3.F32
M2_PCIE_RX0_N: J12.47, U3.D25
M2_PCIE_RX0_P: J12.49, U3.D24
M2_PCIE_RX1_N: J12.35, U3.B24
M2_PCIE_RX1_P: J12.37, U3.B25
M2_PCIE_RX2_N: J12.23, U3.C26
M2_PCIE_RX2_P: J12.25, U3.C27
M2_PCIE_RX3_N: J12.11, U3.A27
M2_PCIE_RX3_P: J12.13, U3.A26
M2_PCIE_TX0_N: C351.2, J12.41
M2_PCIE_TX0_N_AC: C351.1, U3.H25
M2_PCIE_TX0_P: C350.2, J12.43
M2_PCIE_TX0_P_AC: C350.1, U3.H24
M2_PCIE_TX1_N: C353.2, J12.29
M2_PCIE_TX1_N_AC: C353.1, U3.K24
M2_PCIE_TX1_P: C352.2, J12.31
M2_PCIE_TX1_P_AC: C352.1, U3.K25
M2_PCIE_TX2_N: C355.2, J12.17
M2_PCIE_TX2_N_AC: C355.1, U3.G26
M2_PCIE_TX2_P: C354.2, J12.19
M2_PCIE_TX2_P_AC: C354.1, U3.G27
M2_PCIE_TX3_N: C357.2, J12.5
M2_PCIE_TX3_N_AC: C357.1, U3.J27
M2_PCIE_TX3_P: C356.2, J12.7
M2_PCIE_TX3_P_AC: C356.1, U3.J26
M2_PCIE_WAKE_N: J12.54, U3.A8
M2_PRSNT0: J22.19, U3.A3
M2_PRSNT1: J22.21, U3.L63
M2_SV_EN: J22.37, R321.1, U303.3
M2_SYS_RESET_N: J22.5, U3.L60
M2_THERM_ALERT_N: J22.15, U3.L56
M2_THERM_SHDN_REQ_N: J22.17, U3.G59
M2_UART3_RX_DEBUG: J22.25, U3.K60
M2_UART3_TX_DEBUG: J22.23, U3.H62
M2_USB0_N: J42.A7, J42.B7, U3.F13
M2_USB0_P: J42.A6, J42.B6, U3.F12
M2_USB_VBUS: J42.A4, J42.A9, J42.B4, J42.B9
M2_VDDIN_PWR_BAD_N: J22.9, U3.L55
M2_VIN_HV: U3.B3, U3.B63, U3.C1, U3.C2, U3.C63, U3.C64, U3.C65, U3.D1, U3.D2, U3.D3, U3.D64, U3.D65, U3.E1, U3.E2, U3.E63, U3.E64, U3.E65, U3.F1, U3.F2, U3.F3, U3.F63, U3.F64, U3.F65, U3.G1, U3.G2, U3.G63, U3.G64, U3.G65, U3.H1, U3.H2, U3.H3, U3.H64, U3.H65, U3.J1, U3.J2, U3.J63, U3.J64, U3.J65, U3.K3, U301.17, U301.18, U301.19, U301.20, U301.21, U301.22, U301.23, U301.24
M2_VIN_MV: U3.L22, U3.L23, U3.L26, U3.L27, U3.L30, U3.L31, U3.L34, U3.L35, U3.L38, U3.L39, U302.17, U302.18, U302.19, U302.20, U302.21, U302.22, U302.23, U302.24
M2_VIN_SV: U3.L53, U303.5, U303.6
M3_CARRIER_POWER_ON: J23.3, U4.L62
M3_CC1: J43.A5, R16.1
M3_CC2: J43.B5, R17.1
M3_FAN_PWM: J33.4, U4.K62
M3_FAN_TACH: J33.3, U4.E54
M3_FORCE_RECOVERY_N: J23.11, U4.L10
M3_HV_EN: J23.31, R403.1, U401.6
M3_HV_IMON: J4.23, R402.1, U401.9
M3_HV_PG: J23.33, R404.2, U401.13
M3_I2C3_CLK: J23.27, U4.F53
M3_I2C3_DAT: J23.29, U4.E53
M3_MGBE_REFCLK_N: R441.2, R443.1, U4.F29
M3_MGBE_REFCLK_P: R440.2, R442.1, U4.F28
M3_MODULE_POWER_GOOD: J23.7, U4.L59
M3_MODULE_POWER_ON: J23.1, U4.L54
M3_MODULE_SHDN_N: J23.13, U4.L52
M3_MV_EN: J23.35, R413.1, U402.6
M3_MV_IMON: R412.1, U402.9
M3_MV_PG: J4.15, R414.2, U402.13
M3_OSC_N: R441.1, X4.5
M3_OSC_P: R440.1, X4.4
M3_PCIE_CLKREQ_N: J13.52, U4.L19
M3_PCIE_PERST_N: J13.50, U4.L18
M3_PCIE_REFCLK_N: J13.53, U4.F33
M3_PCIE_REFCLK_P: J13.55, U4.F32
M3_PCIE_RX0_N: J13.47, U4.D25
M3_PCIE_RX0_P: J13.49, U4.D24
M3_PCIE_RX1_N: J13.35, U4.B24
M3_PCIE_RX1_P: J13.37, U4.B25
M3_PCIE_RX2_N: J13.23, U4.C26
M3_PCIE_RX2_P: J13.25, U4.C27
M3_PCIE_RX3_N: J13.11, U4.A27
M3_PCIE_RX3_P: J13.13, U4.A26
M3_PCIE_TX0_N: C451.2, J13.41
M3_PCIE_TX0_N_AC: C451.1, U4.H25
M3_PCIE_TX0_P: C450.2, J13.43
M3_PCIE_TX0_P_AC: C450.1, U4.H24
M3_PCIE_TX1_N: C453.2, J13.29
M3_PCIE_TX1_N_AC: C453.1, U4.K24
M3_PCIE_TX1_P: C452.2, J13.31
M3_PCIE_TX1_P_AC: C452.1, U4.K25
M3_PCIE_TX2_N: C455.2, J13.17
M3_PCIE_TX2_N_AC: C455.1, U4.G26
M3_PCIE_TX2_P: C454.2, J13.19
M3_PCIE_TX2_P_AC: C454.1, U4.G27
M3_PCIE_TX3_N: C457.2, J13.5
M3_PCIE_TX3_N_AC: C457.1, U4.J27
M3_PCIE_TX3_P: C456.2, J13.7
M3_PCIE_TX3_P_AC: C456.1, U4.J26
M3_PCIE_WAKE_N: J13.54, U4.A8
M3_PRSNT0: J23.19, U4.A3
M3_PRSNT1: J23.21, U4.L63
M3_SV_EN: J23.37, R421.1, U403.3
M3_SYS_RESET_N: J23.5, U4.L60
M3_THERM_ALERT_N: J23.15, U4.L56
M3_THERM_SHDN_REQ_N: J23.17, U4.G59
M3_UART3_RX_DEBUG: J23.25, U4.K60
M3_UART3_TX_DEBUG: J23.23, U4.H62
M3_USB0_N: J43.A7, J43.B7, U4.F13
M3_USB0_P: J43.A6, J43.B6, U4.F12
M3_USB_VBUS: J43.A4, J43.A9, J43.B4, J43.B9
M3_VDDIN_PWR_BAD_N: J23.9, U4.L55
M3_VIN_HV: U4.B3, U4.B63, U4.C1, U4.C2, U4.C63, U4.C64, U4.C65, U4.D1, U4.D2, U4.D3, U4.D64, U4.D65, U4.E1, U4.E2, U4.E63, U4.E64, U4.E65, U4.F1, U4.F2, U4.F3, U4.F63, U4.F64, U4.F65, U4.G1, U4.G2, U4.G63, U4.G64, U4.G65, U4.H1, U4.H2, U4.H3, U4.H64, U4.H65, U4.J1, U4.J2, U4.J63, U4.J64, U4.J65, U4.K3, U401.17, U401.18, U401.19, U401.20, U401.21, U401.22, U401.23, U401.24
M3_VIN_MV: U4.L22, U4.L23, U4.L26, U4.L27, U4.L30, U4.L31, U4.L34, U4.L35, U4.L38, U4.L39, U402.17, U402.18, U402.19, U402.20, U402.21, U402.22, U402.23, U402.24
M3_VIN_SV: U4.L53, U403.5, U403.6
MESH_01_N: C159.2, U2.D29
MESH_01_N_AC: C159.1, U1.H29
MESH_01_P: C158.2, U2.D28
MESH_01_P_AC: C158.1, U1.H28
MESH_02_N: C161.2, U3.D29
MESH_02_N_AC: C161.1, U1.K28
MESH_02_P: C160.2, U3.D28
MESH_02_P_AC: C160.1, U1.K29
MESH_03_N: C163.2, U4.D29
MESH_03_N_AC: C163.1, U1.G30
MESH_03_P: C162.2, U4.D28
MESH_03_P_AC: C162.1, U1.G31
MESH_10_N: C259.2, U1.D29
MESH_10_N_AC: C259.1, U2.H29
MESH_10_P: C258.2, U1.D28
MESH_10_P_AC: C258.1, U2.H28
MESH_12_N: C261.2, U3.B28
MESH_12_N_AC: C261.1, U2.K28
MESH_12_P: C260.2, U3.B29
MESH_12_P_AC: C260.1, U2.K29
MESH_13_N: C263.2, U4.B28
MESH_13_N_AC: C263.1, U2.G30
MESH_13_P: C262.2, U4.B29
MESH_13_P_AC: C262.1, U2.G31
MESH_20_N: C359.2, U1.B28
MESH_20_N_AC: C359.1, U3.H29
MESH_20_P: C358.2, U1.B29
MESH_20_P_AC: C358.1, U3.H28
MESH_21_N: C361.2, U2.B28
MESH_21_N_AC: C361.1, U3.K28
MESH_21_P: C360.2, U2.B29
MESH_21_P_AC: C360.1, U3.K29
MESH_23_N: C363.2, U4.C30
MESH_23_N_AC: C363.1, U3.G30
MESH_23_P: C362.2, U4.C31
MESH_23_P_AC: C362.1, U3.G31
MESH_30_N: C459.2, U1.C30
MESH_30_N_AC: C459.1, U4.H29
MESH_30_P: C458.2, U1.C31
MESH_30_P_AC: C458.1, U4.H28
MESH_31_N: C461.2, U2.C30
MESH_31_N_AC: C461.1, U4.K28
MESH_31_P: C460.2, U2.C31
MESH_31_P_AC: C460.1, U4.K29
MESH_32_N: C463.2, U3.C30
MESH_32_N_AC: C463.1, U4.G30
MESH_32_P: C462.2, U3.C31
MESH_32_P_AC: C462.1, U4.G31
PANEL_USB_N: J3.2, U1.C10
PANEL_USB_P: J3.3, U1.C11
PMBUS_ALERT_N: R703.2, U501.6, U601.6
PMBUS_CLK: J4.5, R701.2, U501.3, U601.3
PMBUS_DAT: J4.7, R702.2, U501.2, U601.2
QSFP_INT_N: J2.28, J4.35
QSFP_LPMODE: J2.31, J4.37
QSFP_MODPRS_N: J2.27, J4.33
QSFP_MODSEL_N: J2.8, J4.25
QSFP_RESET_N: J2.9, J4.27
QSFP_SCL: J2.11, J4.29
QSFP_SDA: J2.12, J4.31
Q_RX1_N: J2.18, U1.A31
Q_RX1_P: J2.17, U1.A30
Q_RX2_N: J2.21, U2.A31
Q_RX2_P: J2.22, U2.A30
Q_RX3_N: J2.15, U3.A31
Q_RX3_P: J2.14, U3.A30
Q_RX4_N: J2.24, U4.A31
Q_RX4_P: J2.25, U4.A30
Q_TX1_N: J2.37, U1.J31
Q_TX1_P: J2.36, U1.J30
Q_TX2_N: J2.2, U2.J31
Q_TX2_P: J2.3, U2.J30
Q_TX3_N: J2.34, U3.J31
Q_TX3_P: J2.33, U3.J30
Q_TX4_N: J2.5, U4.J31
Q_TX4_P: J2.6, U4.J30
U101_DVDT: C103.1, U101.15
U101_ILIM: R101.1, U101.8
U102_DVDT: C113.1, U102.15
U102_ILIM: R111.1, U102.8
U103_CT: C122.1, U103.4
U201_DVDT: C203.1, U201.15
U201_ILIM: R201.1, U201.8
U202_DVDT: C213.1, U202.15
U202_ILIM: R211.1, U202.8
U203_CT: C222.1, U203.4
U301_DVDT: C303.1, U301.15
U301_ILIM: R301.1, U301.8
U302_DVDT: C313.1, U302.15
U302_ILIM: R311.1, U302.8
U303_CT: C322.1, U303.4
U401_DVDT: C403.1, U401.15
U401_ILIM: R401.1, U401.8
U402_DVDT: C413.1, U402.15
U402_ILIM: R411.1, U402.8
U403_CT: C422.1, U403.4
U501_ADRSEL: R509.1, U501.31
U501_AVIN: C523.1, R501.2, U501.26
U501_BOOT: C522.1, U501.7
U501_BP1V5: C521.1, R504.1, R507.1, U501.4
U501_DRTN: C521.2, U501.5
U501_MSEL1: R506.1, U501.32
U501_MSEL2: R507.2, R508.1, U501.29
U501_SW: C522.2, L501.1, U501.8, U501.9, U501.10, U501.11, U501.12
U501_VDD5: C531.1, U501.28
U501_VSEL: R504.2, R505.1, U501.30
U601_ADRSEL: R610.1, U601.31
U601_AVIN: C623.1, R601.2, U601.26
U601_BOOT: C622.1, U601.7
U601_BP1V5: C621.1, R605.1, R608.1, U601.4
U601_DRTN: C621.2, U601.5
U601_MSEL1: R607.1, U601.32
U601_MSEL2: R608.2, R609.1, U601.29
U601_SW: C622.2, L601.1, U601.8, U601.9, U601.10, U601.11, U601.12
U601_VDD5: C631.1, U601.28
U601_VSEL: R605.2, R606.1, U601.30
VIN_12V: C101.1, C102.1, C201.1, C202.1, C301.1, C302.1, C401.1, C402.1, C501.1, C502.1, C503.1, C504.1, C505.1, C601.1, C602.1, C603.1, C604.1, C605.1, J1.5, J1.6, J1.7, J1.8, J5.5, J5.6, J5.7, J5.8, J30.2, J31.2, J32.2, J33.2, R501.1, R601.1, R603.1, U101.1, U101.2, U101.3, U101.16, U101.25, U201.1, U201.2, U201.3, U201.16, U201.25, U301.1, U301.2, U301.3, U301.16, U301.25, U401.1, U401.2, U401.3, U401.16, U401.25, U501.21, U501.22, U501.23, U501.24, U501.25, U601.21, U601.22, U601.23, U601.24, U601.25

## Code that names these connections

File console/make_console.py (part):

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def buck(base, gx, vout, en, pg, straps, en_parts):
    u = f"U{base}"
    pins = {str(n): "GND" for n in (*range(13, 21), 36, 37, 39, 40, 41)}   # PGND, NC, AGND, BCX_CLK/DAT (stand-alone), pad
    pins.update({str(n): "VIN_12V" for n in range(21, 26)})
    pins.update({str(n): f"{u}_SW" for n in range(8, 13)})
    pins.update({"1": pg, "2": "PMBUS_DAT", "3": "PMBUS_CLK", "4": f"{u}_BP1V5", "5": f"{u}_DRTN", "6": "PMBUS_ALERT_N",
                 "7": f"{u}_BOOT", "26": f"{u}_AVIN", "27": en, "28": f"{u}_VDD5", "29": f"{u}_MSEL2", "30": f"{u}_VSEL",
                 "31": f"{u}_ADRSEL", "32": f"{u}_MSEL1", "33": vout, "34": "GND"})      # 35 VSHARE + 38 SYNC float
    add("Console", "TI_RVF0040A_LQFN-CLIP-40_5x7mm_P0.5mm_EP3.3x5.3mm", u, gx + 5, 224, 0, "TPS546B24ARVFR (C3189423)", pins)
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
